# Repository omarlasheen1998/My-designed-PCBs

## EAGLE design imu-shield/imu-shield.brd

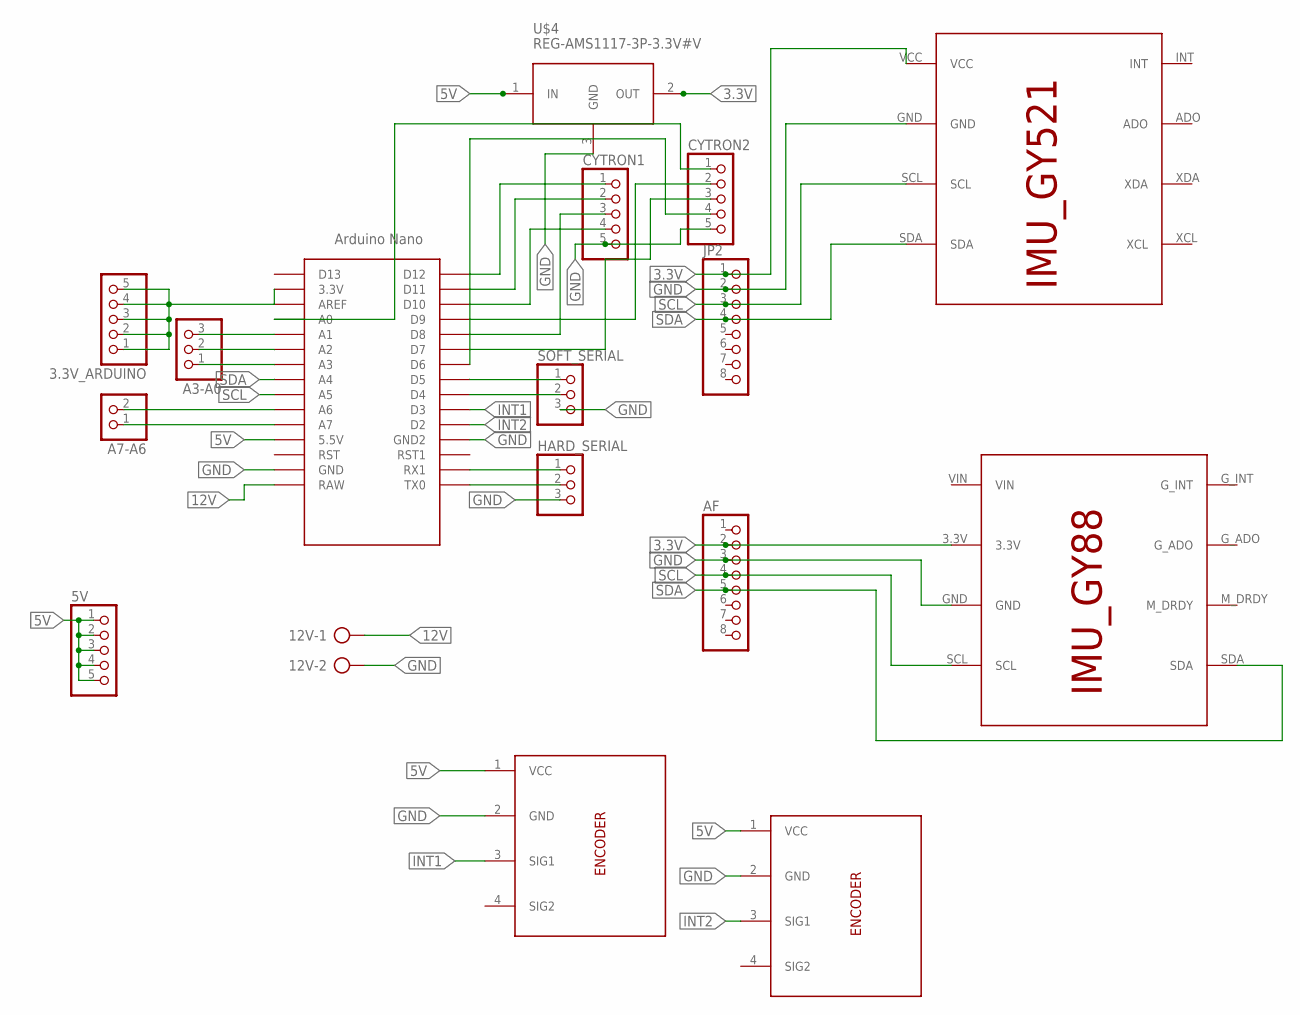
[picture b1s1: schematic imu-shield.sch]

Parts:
3.3V_ARDUINO, 5V: PINHD-1X5; 1X05
12V: AK300/2
A3-A0: PINHD-1X3; 1X03
A7-A6: PINHD-1X2; 1X02
AF: PINHD-1X8; 1X08
CYTRON1, CYTRON2: PINHD-1X5; 1X05
ENCODER1, ENCODER2: ENCODER; 1X04
HARD_SERIAL: PINHD-1X3; 1X03
JP2: PINHD-1X8; 1X08
SOFT_SERIAL: PINHD-1X3; 1X03
U$1: NANO
U$2: IMU_ROBOCON; IMU_GY521
U$3: IMU_MINESWEEPER; IMU_GY88
U$4: REG-AMS1117-3P-3.3V#V; REG-AMS1117-3P#V

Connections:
3.3V: AF.2, JP2.1, U$2.VCC, U$3.3.3V, U$4.2 (OUT)
5V: 5V.1, 5V.2, 5V.3, 5V.4, 5V.5, ENCODER1.1 (VCC), ENCODER2.1 (VCC), U$1.5V (5.5V), U$4.1 (IN)
12V: 12V.1, U$1.RAW
GND: 12V.2, AF.3, CYTRON1.5, CYTRON2.5, ENCODER1.2 (GND), ENCODER2.2 (GND), HARD_SERIAL.3, JP2.2, SOFT_SERIAL.3, U$1.GND, U$1.GND1 (GND2), U$2.GND, U$3.GND, U$4.3 (GND)
INT1: ENCODER2.3 (SIG1), U$1.D3
INT2: ENCODER1.3 (SIG1), U$1.D2
unnamed: SOFT_SERIAL.1, U$1.D5
unnamed: SOFT_SERIAL.2, U$1.D4
unnamed: HARD_SERIAL.1, U$1.RX1
unnamed: HARD_SERIAL.2, U$1.TX0
unnamed: CYTRON1.1, U$1.D12
unnamed: CYTRON1.2, U$1.D11
unnamed: CYTRON1.4, U$1.D10
unnamed: CYTRON2.2, U$1.D9
unnamed: CYTRON1.3, U$1.D8
unnamed: CYTRON2.3, U$1.D7
unnamed: CYTRON2.4, U$1.D6
unnamed: CYTRON2.1, U$1.A0
unnamed: A3-A0.1, U$1.A3
unnamed: A3-A0.2, U$1.A2
unnamed: A3-A0.3, U$1.A1
unnamed: A7-A6.1, U$1.A7
unnamed: A7-A6.2, U$1.A6
unnamed: 3.3V_ARDUINO.1, 3.3V_ARDUINO.2, 3.3V_ARDUINO.3, 3.3V_ARDUINO.4, 3.3V_ARDUINO.5, U$1.3.3V
SCL: AF.4, JP2.3, U$1.A5, U$2.SCL, U$3.SCL
SDA: AF.5, JP2.4, U$1.A4, U$2.SDA, U$3.SDA

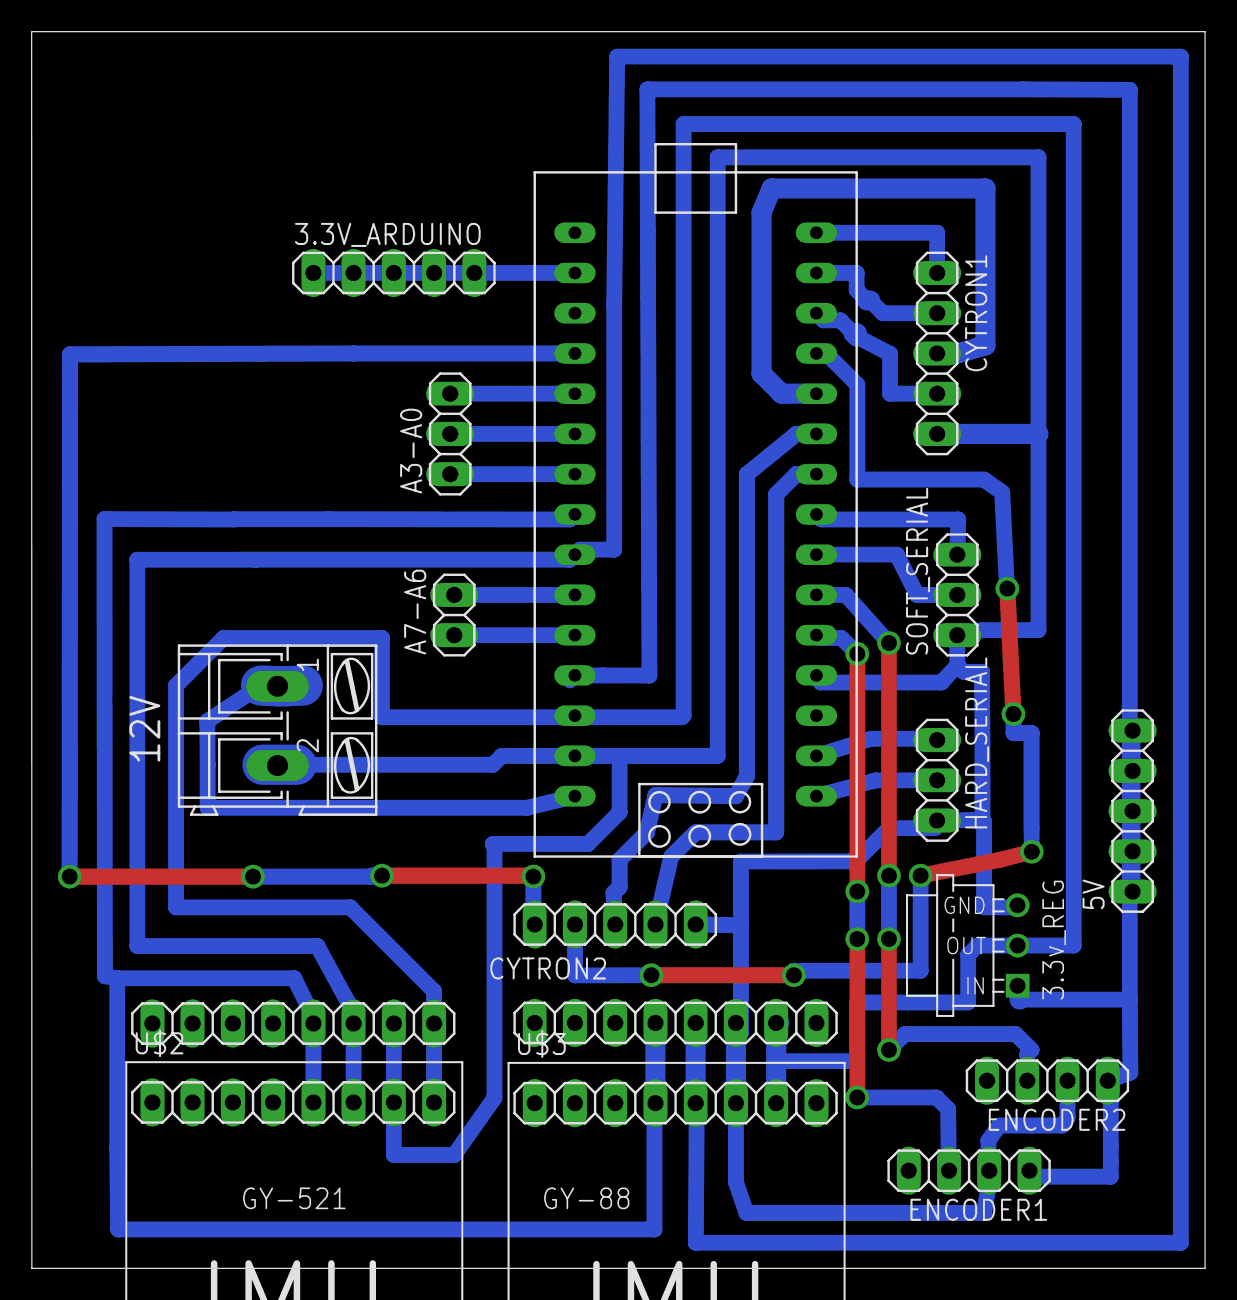
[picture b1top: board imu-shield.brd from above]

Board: 2 copper layers, 74.1 x 78.1 mm, 17 parts (0 on the bottom side), 26 nets.

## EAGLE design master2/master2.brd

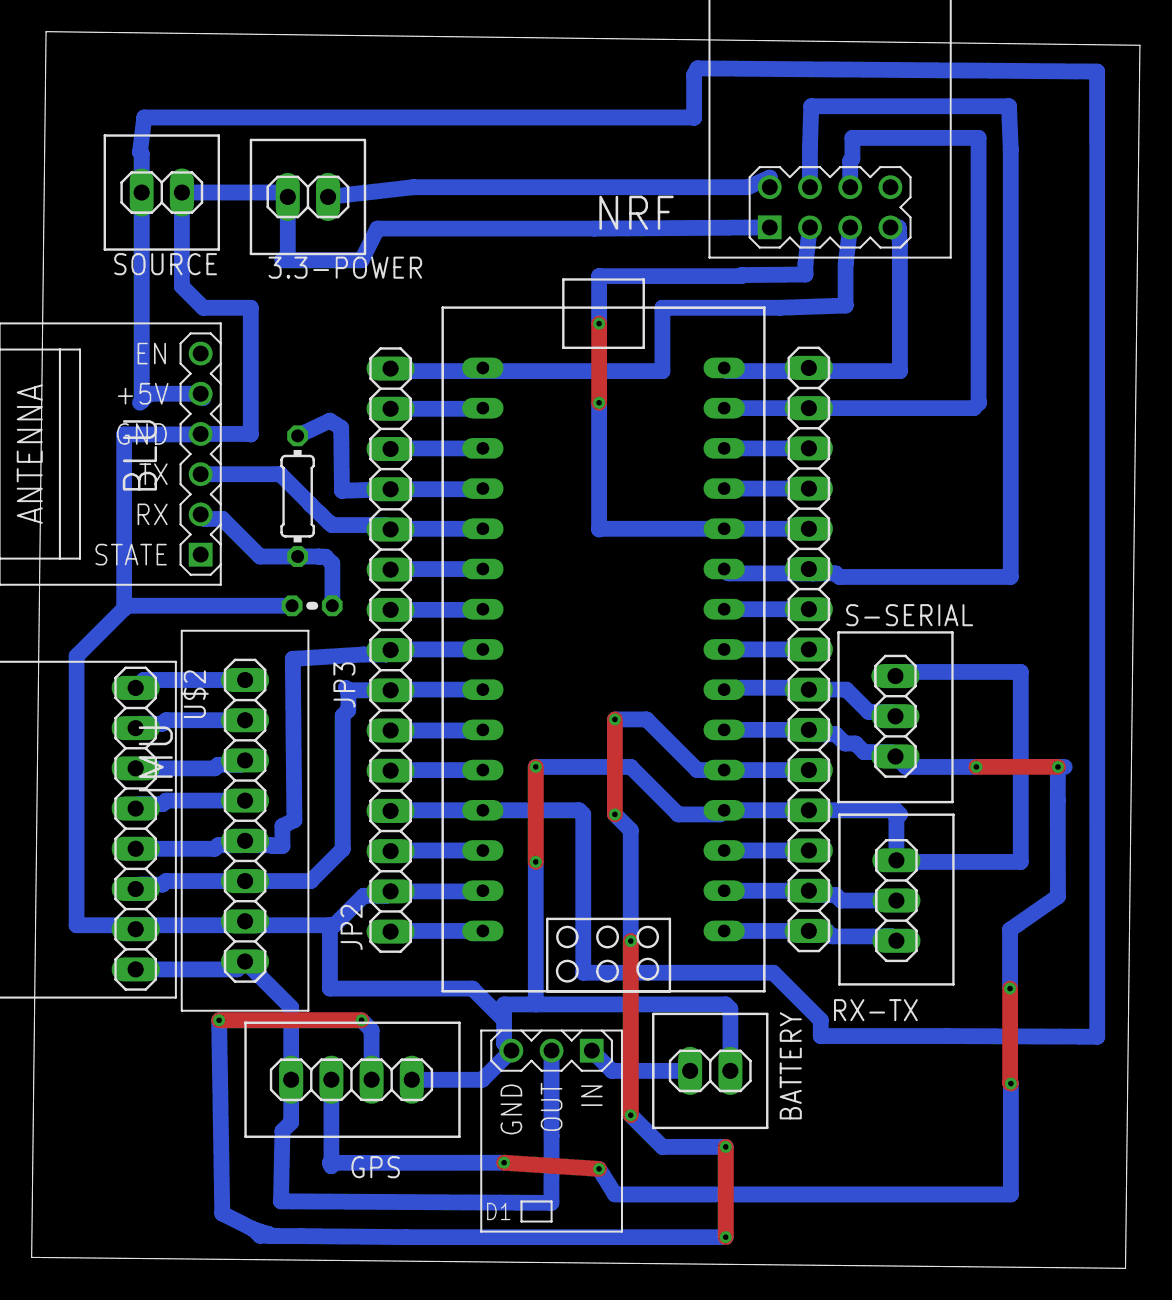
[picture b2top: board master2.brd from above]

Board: 2 copper layers, 70.0 x 78.1 mm, 16 parts (0 on the bottom side), 37 nets.

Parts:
3.3-POWER: 1X02_DATA
BATTERY: 1X02_DATA
GPS: 1X04_DATA
JP1, JP2: 1X15
JP3: 1X08_DATA
M1: WIRELESS-NRF24L01-PA-EXT
R1: 1k; 0204/7
R2: 2.2k; 0204V
RX-TX: 1X03_DATA
S-SERIAL: 1X03_DATA
SOURCE: 1X02_DATA
U$1: ARDUINO_NANO; NANO
U$2: IMU_ROBOCON; IMU_GY521
U$3: BLUETOOTH-HC-05; WIRELESS-BLUETOOTH-HC-05
U$4: REG-AMS1117-3P-3.3V; REG-AMS1117-3P

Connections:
3.3: GPS.4, JP3.8, U$2.VCC, U$4.2
3.3-POWER: 3.3-POWER.2, M1.2
A0: JP2.12, R1.2, U$1.A0
A1: JP2.11, U$1.A1, U$3.3
D2: GPS.2, JP1.11, U$1.D2
D3: GPS.3, JP1.10, S-SERIAL.3, U$1.D3
D4: JP1.9, S-SERIAL.2, U$1.D4
D5: JP1.8, U$1.D5
D6: JP1.7, U$1.D6
D7: JP1.6, M1.4, U$1.D7
D8: JP1.5, M1.3, U$1.D8
GND: 3.3-POWER.1, BATTERY.2, GPS.1, JP1.12, JP2.2, JP3.7, M1.1, R2.1, RX-TX.3, S-SERIAL.1, SOURCE.2, U$1.GND, U$1.GND1, U$2.GND, U$3.4, U$4.3
MISO: JP1.1, M1.7, U$1.D12
MOSI: JP1.2, M1.6, U$1.D11
unnamed: JP2.1, U$1.RAW
unnamed: R1.1, R2.2, U$3.2
unnamed: JP2.3, U$1.RST
unnamed: JP1.3, U$1.D10
unnamed: JP2.5, U$1.A7
unnamed: JP2.6, U$1.A6
unnamed: JP1.14, RX-TX.2, U$1.RX1
unnamed: JP3.1, U$2.INT
unnamed: JP2.9, U$1.A3
unnamed: JP2.10, U$1.A2
unnamed: JP3.2, U$2.ADO
unnamed: JP3.3, U$2.XCL
unnamed: JP2.13, U$1.AREF
unnamed: JP2.14, U$1.3.3V
unnamed: JP3.4, U$2.XDA
unnamed: JP1.4, U$1.D9
unnamed: JP1.13, U$1.RST1
unnamed: JP1.15, RX-TX.1, U$1.TX0
unnamed: BATTERY.1, U$4.1
S-CLC: JP2.15, M1.5, U$1.D13
SCL: JP2.7, JP3.6, U$1.A5, U$2.SCL
SDA: JP2.8, JP3.5, U$1.A4, U$2.SDA
VCC: JP2.4, SOURCE.1, U$1.5V, U$3.5

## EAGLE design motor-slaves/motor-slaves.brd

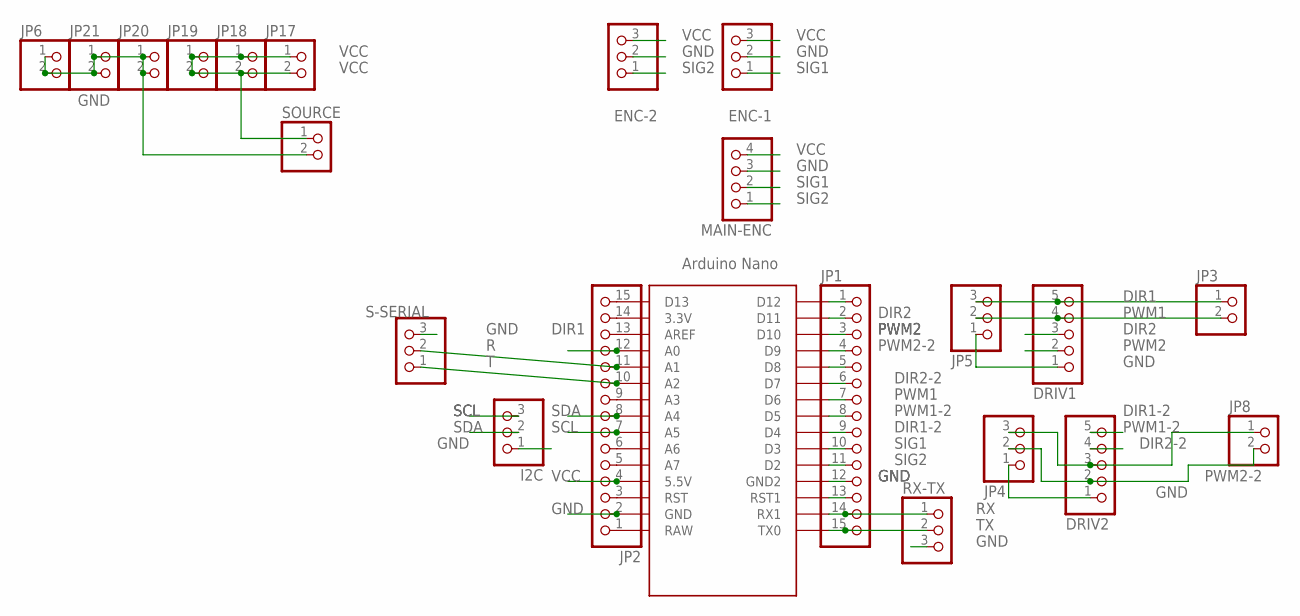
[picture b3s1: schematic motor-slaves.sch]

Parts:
DRIV1, DRIV2: PINHD-5_DATA; 1X05_DATA
ENC-1, ENC-2: PINHD-3_DATA; 1X03_DATA
I2C: PINHD-3_DATA; 1X03_DATA
JP1, JP2: PINHD-1X15; 1X15
JP3, JP8: PINHD-2_DATA; 1X02_DATA
JP4, JP5: PINHD-3_DATA; 1X03_DATA
JP6, JP17, JP18, JP19, JP20, JP21: PINHD-1X2; 1X02
MAIN-ENC: PINHD-4_DATA; 1X04_DATA
RX-TX: PINHD-3_DATA; 1X03_DATA
S-SERIAL: PINHD-3_DATA; 1X03_DATA
SOURCE: PINHD-1X2; 1X02
U$1: ARDUINO_NANO; NANO

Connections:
DIR1: DRIV1.5, JP2.12, JP3.1, JP5.3, U$1.A0
DIR1-2: DRIV2.5, JP1.9, U$1.D4
DIR2: DRIV1.3, JP1.2, U$1.D11
DIR2-2: DRIV2.3, JP1.6, JP4.3, JP8.1, U$1.D7
GND: DRIV1.1, DRIV2.1, ENC-1.2, ENC-2.2, I2C.1, JP1.12, JP2.2, JP4.1, JP5.1, JP6.1, JP6.2, JP20.1, JP20.2, JP21.1, JP21.2, MAIN-ENC.3, RX-TX.3, S-SERIAL.3, SOURCE.2, U$1.GND, U$1.GND1 (GND2)
unnamed: JP1.1, U$1.D12
unnamed: JP1.5, U$1.D8
unnamed: JP1.13, U$1.RST1
unnamed: JP2.1, U$1.RAW
unnamed: JP2.3, U$1.RST
unnamed: JP2.5, U$1.A7
unnamed: JP2.6, U$1.A6
unnamed: JP2.9, U$1.A3
unnamed: JP2.13, U$1.AREF
unnamed: JP2.14, U$1.3.3V
unnamed: JP2.15, U$1.D13
PWM1: DRIV1.4, JP1.7, JP3.2, JP5.2, U$1.D6
PWM1-2: DRIV2.4, JP1.8, U$1.D5
PWM2: DRIV1.2, JP1.3, U$1.D10
PWM2-2: DRIV2.2, JP1.4, JP4.2, JP8.2, U$1.D9
R: JP2.11, S-SERIAL.2, U$1.A1
RX: JP1.14, RX-TX.1, U$1.RX1
SCL: I2C.3, JP2.7, U$1.A5
SDA: I2C.2, JP2.8, U$1.A4
SIG1: ENC-1.1, JP1.10, MAIN-ENC.2, U$1.D3
SIG2: ENC-2.1, JP1.11, MAIN-ENC.1, U$1.D2
T: JP2.10, S-SERIAL.1, U$1.A2
TX: JP1.15, RX-TX.2, U$1.TX0
VCC: ENC-1.3, ENC-2.3, JP2.4, JP17.1, JP17.2, JP18.1, JP18.2, JP19.1, JP19.2, MAIN-ENC.4, SOURCE.1, U$1.5V (5.5V)

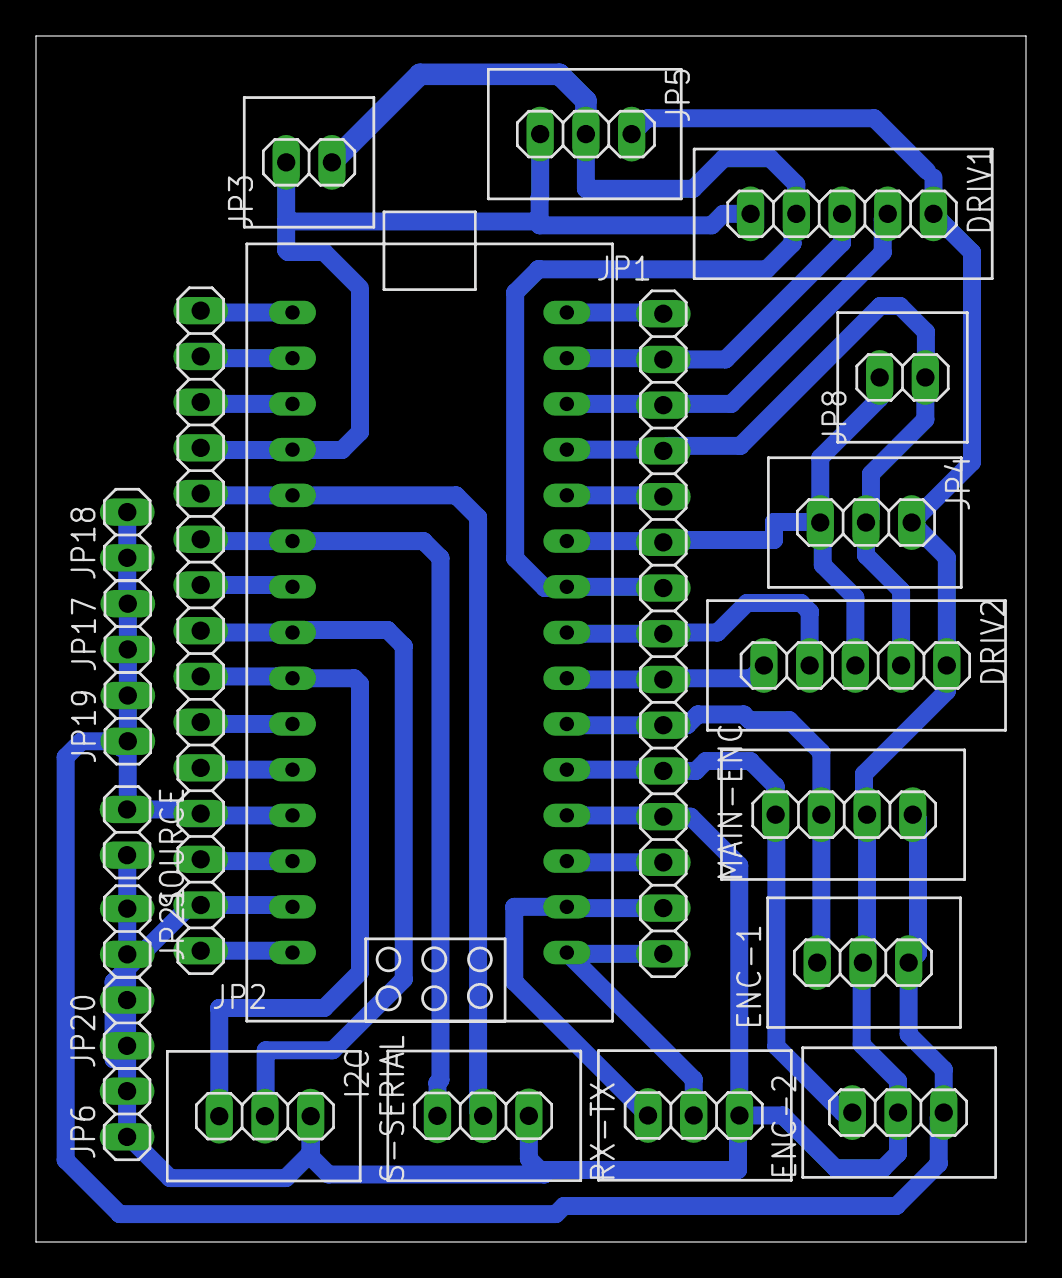
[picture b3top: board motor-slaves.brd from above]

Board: 2 copper layers, 55.0 x 67.0 mm, 22 parts (0 on the bottom side), 29 nets.

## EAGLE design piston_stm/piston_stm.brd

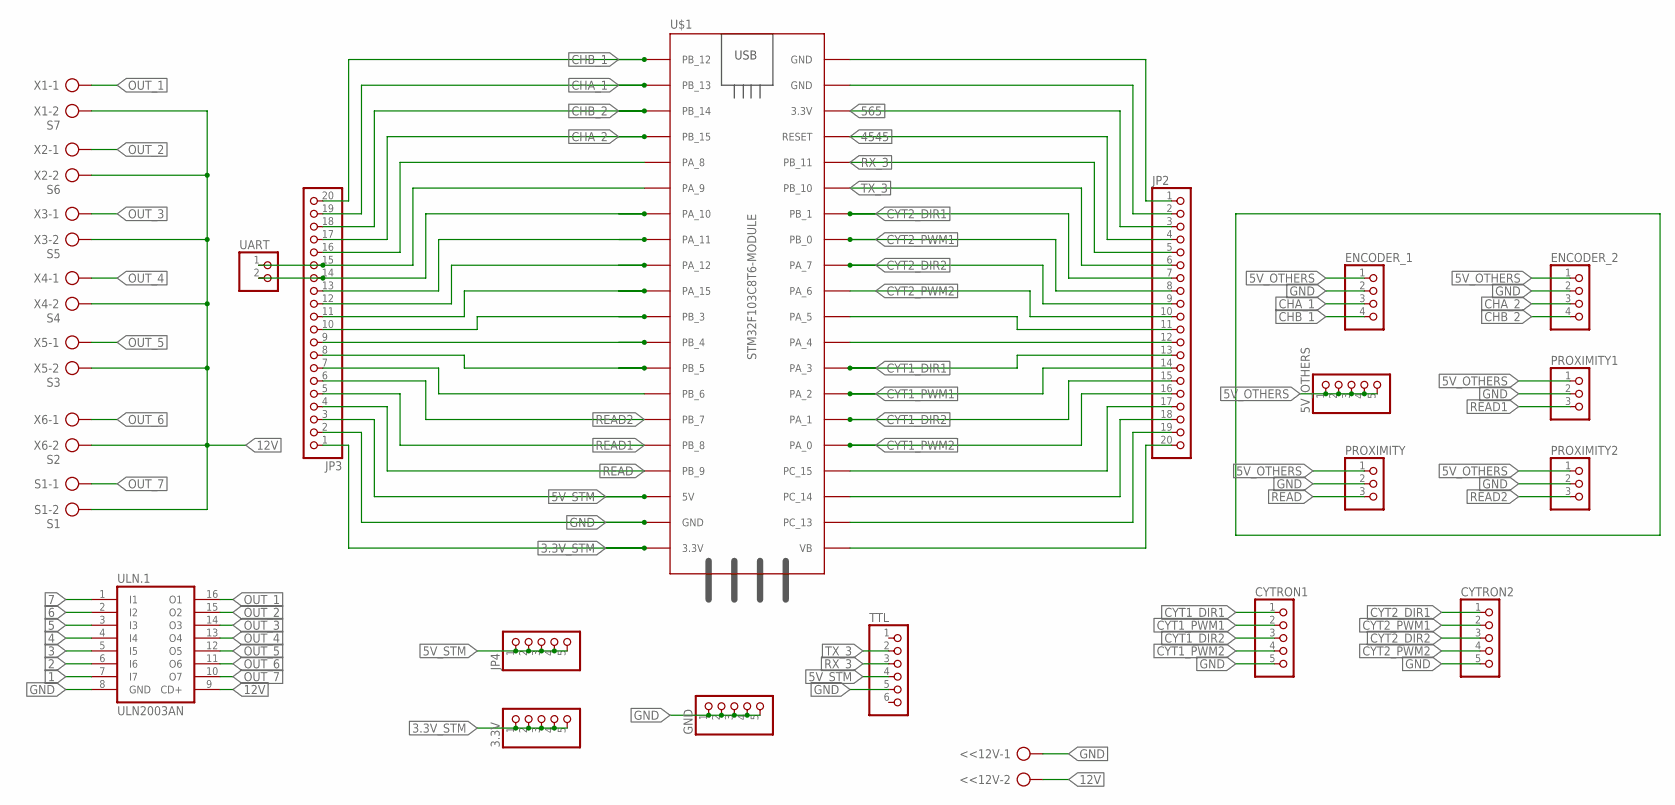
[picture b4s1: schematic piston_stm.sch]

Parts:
3.3V, 5V_OTHERS: PINHD-1X5; 1X05
<<12V: AK300/2
CYTRON1, CYTRON2: PINHD-5_DATA; DATA_5
ENCODER_1, ENCODER_2: PINHD-4_DATA; DATA_4
GND: PINHD-1X5; 1X05
JP2, JP3: PINHD-1X20; 1X20
JP4: PINHD-1X5; 1X05
PROXIMITY, PROXIMITY1, PROXIMITY2: PINHD-3_DATA; DATA_3
S1: S1; AK300/2
TTL: PINHD-6_DATA; DATA_6
U$1: STM32F103C8T6-MODULE
UART: PINHD-2_DATA; DATA_2
ULN.1: ULN2003AN; DIL16
X1: S7; AK300/2
X2: S6; AK300/2
X3: S5; AK300/2
X4: S4; AK300/2
X5: S3; AK300/2
X6: S2; AK300/2

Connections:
0: JP3.7, U$1.PB_6
1: JP3.13, U$1.PA_11, ULN.1.7 (I7)
2: JP3.12, U$1.PA_12, ULN.1.6 (I6)
3: JP3.11, U$1.PA_15, ULN.1.5 (I5)
3.3V_STM: 3.3V.1, 3.3V.2, 3.3V.3, 3.3V.4, 3.3V.5, JP3.1, U$1.3.3V_1 (3.3V)
4: JP3.10, U$1.PB_3, ULN.1.4 (I4)
5: JP3.9, U$1.PB_4, ULN.1.3 (I3)
5V_OTHERS: 5V_OTHERS.1, 5V_OTHERS.2, 5V_OTHERS.3, 5V_OTHERS.4, 5V_OTHERS.5, ENCODER_1.1, ENCODER_2.1, PROXIMITY.1, PROXIMITY1.1, PROXIMITY2.1
5V_STM: JP3.3, JP4.1, JP4.2, JP4.3, JP4.4, JP4.5, TTL.4, U$1.5V
6: JP3.8, U$1.PB_5, ULN.1.2 (I2)
7: JP2.12, U$1.PA_4, ULN.1.1 (I1)
12V: <<12V.2, S1.2, ULN.1.9 (CD+), X1.2, X2.2, X3.2, X4.2, X5.2, X6.2
565: JP2.3, U$1.3.3V_2 (3.3V)
4545: JP2.4, U$1.RESET
54454: JP3.14, U$1.PA_10, UART.2
CHA_1: ENCODER_1.3, JP3.19, U$1.PB_13
CHA_2: ENCODER_2.3, JP3.17, U$1.PB_15
CHB_1: ENCODER_1.4, JP3.20, U$1.PB_12
CHB_2: ENCODER_2.4, JP3.18, U$1.PB_14
CYT1_DIR1: CYTRON1.1, JP2.13, U$1.PA_3
CYT1_DIR2: CYTRON1.3, JP2.15, U$1.PA_1
CYT1_PWM1: CYTRON1.2, JP2.14, U$1.PA_2
CYT1_PWM2: CYTRON1.4, JP2.16, U$1.PA_0
CYT2_DIR1: CYTRON2.1, JP2.7, U$1.PB_1
CYT2_DIR2: CYTRON2.3, JP2.9, U$1.PA_7
CYT2_PWM1: CYTRON2.2, JP2.8, U$1.PB_0
CYT2_PWM2: CYTRON2.4, JP2.10, U$1.PA_6
GND: <<12V.1, CYTRON1.5, CYTRON2.5, ENCODER_1.2, ENCODER_2.2, GND.1, GND.2, GND.3, GND.4, GND.5, JP2.1, JP2.2, JP3.2, PROXIMITY.2, PROXIMITY1.2, PROXIMITY2.2, TTL.5, U$1.GND_1 (GND), U$1.GND_2 (GND), U$1.GND_3 (GND), ULN.1.8 (GND)
unnamed: JP2.11, U$1.PA_5
unnamed: JP2.20, U$1.VB
unnamed: JP2.19, U$1.PC_13
unnamed: JP2.18, U$1.PC_14
unnamed: JP2.17, U$1.PC_15
unnamed: JP3.16, U$1.PA_8
unnamed: JP3.15, U$1.PA_9, UART.1
OUT_1: ULN.1.16 (O1), X1.1
OUT_2: ULN.1.15 (O2), X2.1
OUT_3: ULN.1.14 (O3), X3.1
OUT_4: ULN.1.13 (O4), X4.1
OUT_5: ULN.1.12 (O5), X5.1
OUT_6: ULN.1.11 (O6), X6.1
OUT_7: S1.1, ULN.1.10 (O7)
READ: JP3.4, PROXIMITY.3, U$1.PB_9
READ1: JP3.5, PROXIMITY1.3, U$1.PB_8
READ2: JP3.6, PROXIMITY2.3, U$1.PB_7
RX_3: JP2.5, TTL.3, U$1.PB_11
TX_3: JP2.6, TTL.2, U$1.PB_10

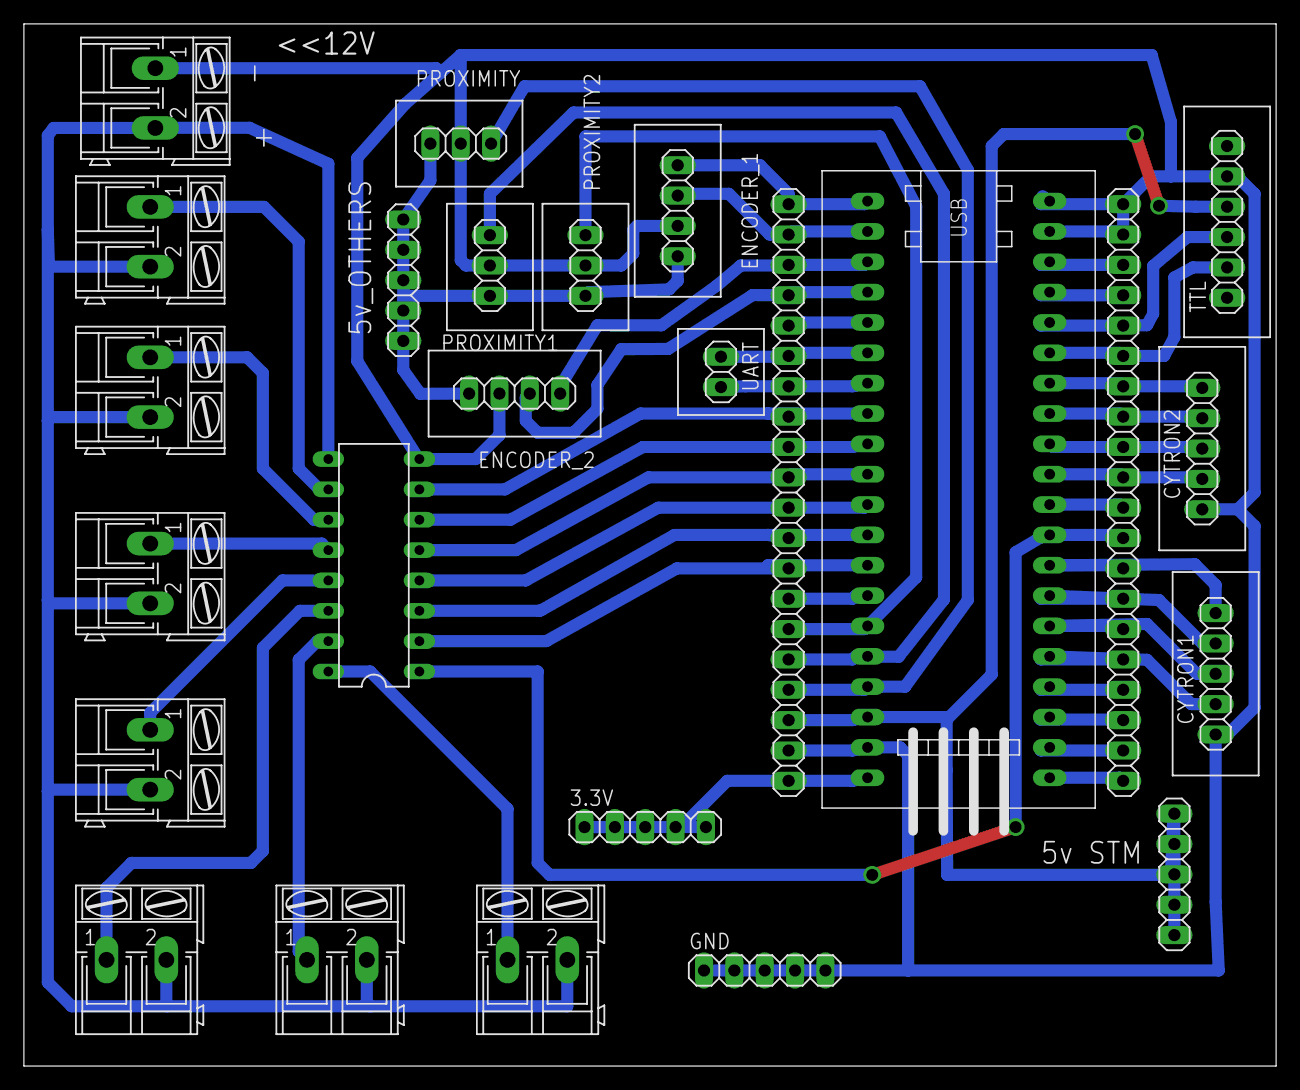
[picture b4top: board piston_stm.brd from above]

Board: 2 copper layers, 104.8 x 87.2 mm, 25 parts (0 on the bottom side), 47 nets.

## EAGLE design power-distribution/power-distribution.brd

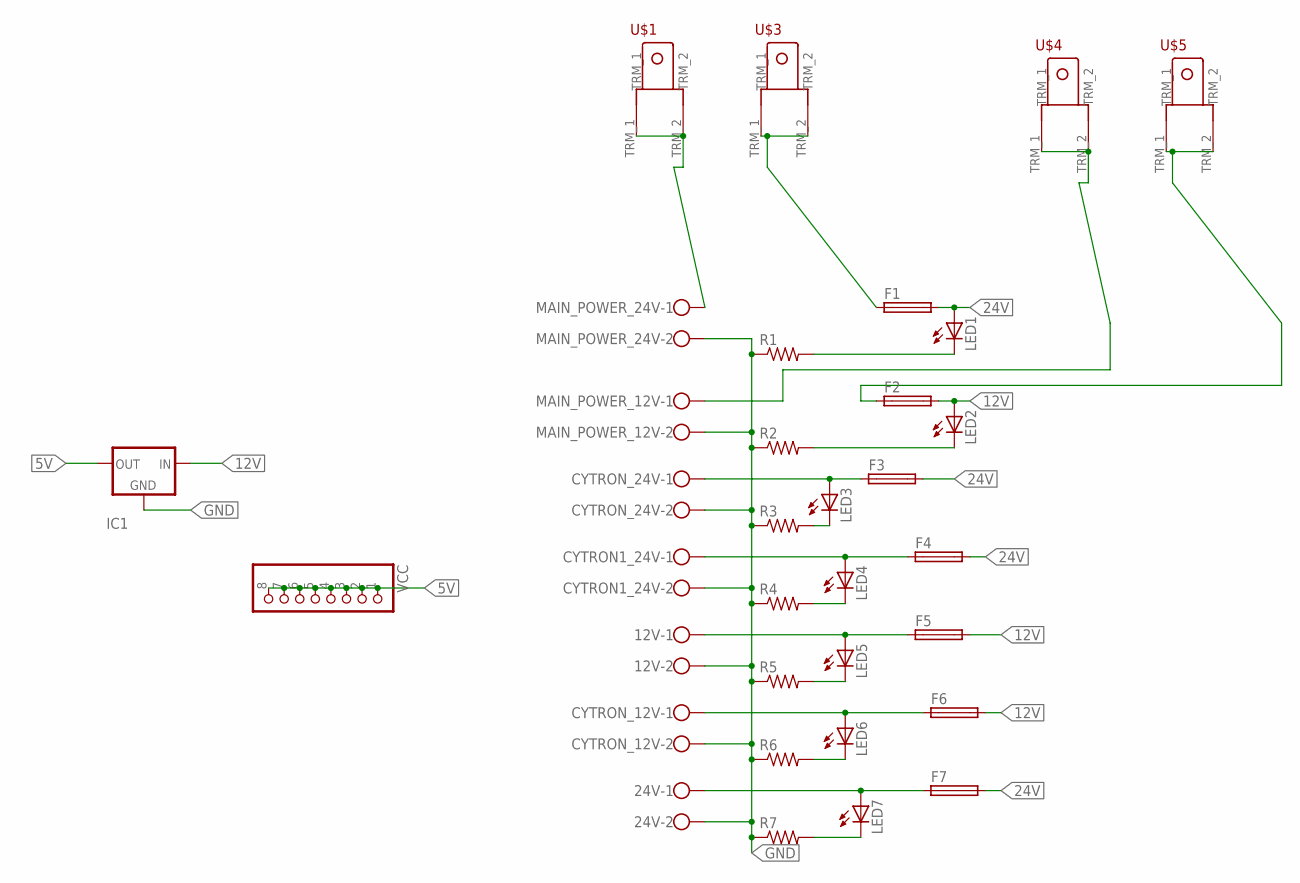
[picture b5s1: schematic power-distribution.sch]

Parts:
12V, 24V: W237-113
CYTRON1_24V: W237-113
CYTRON_12V, CYTRON_24V: W237-113
F1, F2, F3, F4, F5, F6, F7: SH22,5A
IC1: 79XX-TO3; TO3-79
LED1, LED2: LED5MM
LED3, LED4, LED5, LED6, LED7: LED3MM
MAIN_POWER_12V, MAIN_POWER_24V: W237-113
R1, R3, R4, R6, R7: R-US_0204/5; 0204/5
R2: R-US_0207/12; 0207/12
R5: R-US_0207/10; 0207/10
U$1, U$3, U$4, U$5: TERMINAL_EDITED
VCC: PINHD-1X8; 1X08

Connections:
5V: IC1.1 (OUT), VCC.1, VCC.2, VCC.3, VCC.4, VCC.5, VCC.6, VCC.7, VCC.8
12V: F2.2, F5.2, F6.2, IC1.3 (IN), LED2.A
24V: F1.2, F3.2, F4.2, F7.2, LED1.A
GND: 12V.2, 24V.2, CYTRON1_24V.2, CYTRON_12V.2, CYTRON_24V.2, IC1.2 (GND), MAIN_POWER_12V.2, MAIN_POWER_24V.2, R1.1, R2.1, R3.1, R4.1, R5.1, R6.1, R7.1
unnamed: CYTRON_12V.1, F6.1, LED6.A
unnamed: LED1.K (C), R1.2
unnamed: MAIN_POWER_24V.1, U$1.TRM_1, U$1.TRM_2
unnamed: LED2.K (C), R2.2
unnamed: MAIN_POWER_12V.1, U$4.TRM_1, U$4.TRM_2
unnamed: 24V.1, F7.1, LED7.A
unnamed: CYTRON_24V.1, F3.1, LED3.A
unnamed: LED3.K (C), R3.2
unnamed: CYTRON1_24V.1, F4.1, LED4.A
unnamed: LED4.K (C), R4.2
unnamed: 12V.1, F5.1, LED5.A
unnamed: LED5.K (C), R5.2
unnamed: F1.1, U$3.TRM_1, U$3.TRM_2
unnamed: F2.1, U$5.TRM_1, U$5.TRM_2
unnamed: LED6.K (C), R6.2
unnamed: LED7.K (C), R7.2

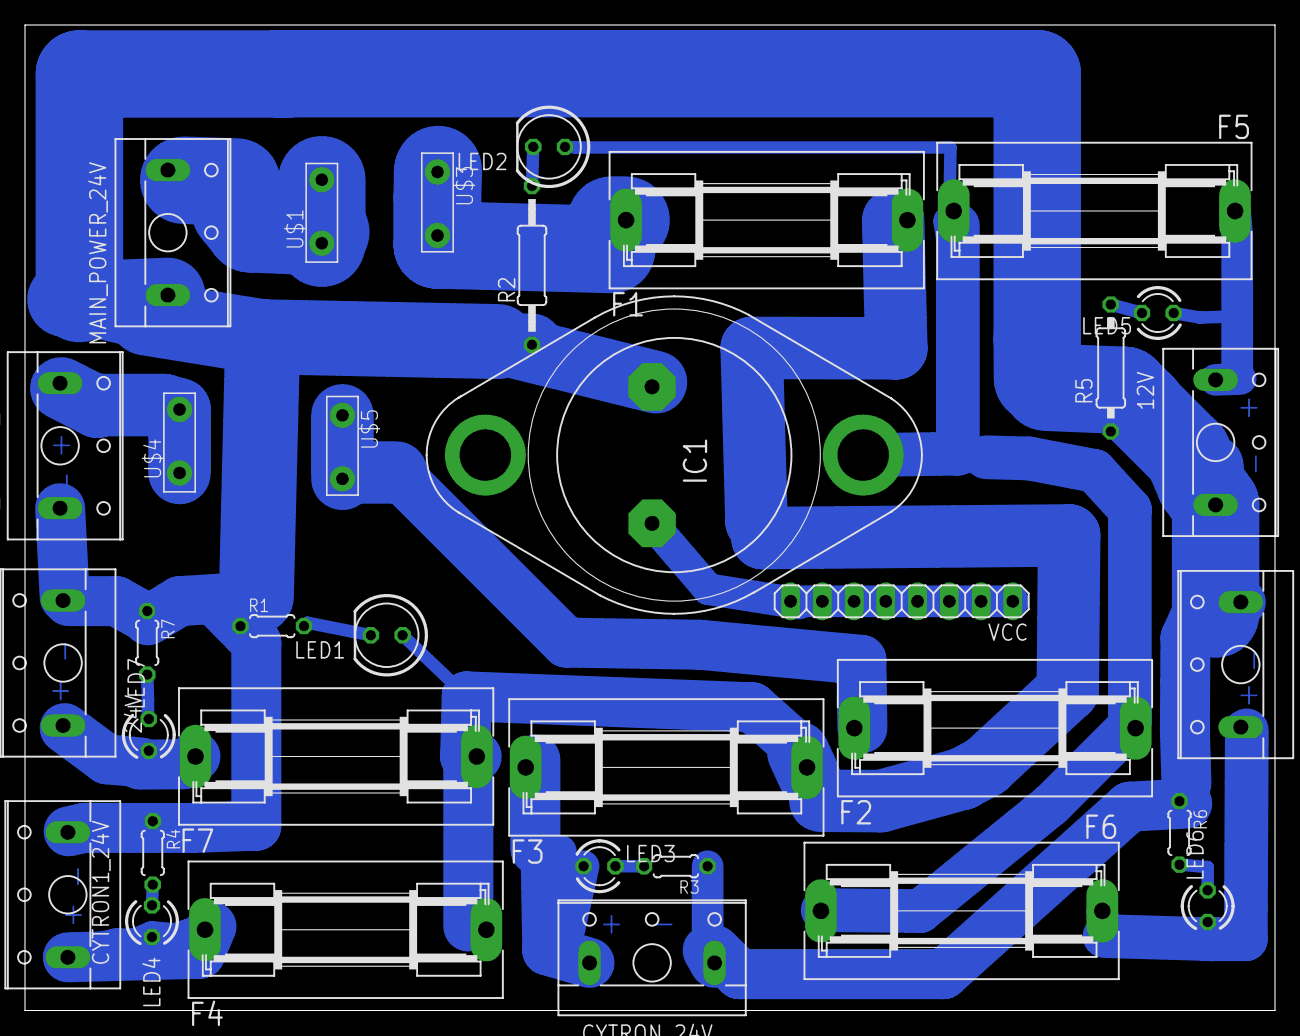
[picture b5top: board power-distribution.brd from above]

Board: 2 copper layers, 100.0 x 78.8 mm, 34 parts (0 on the bottom side), 20 nets.

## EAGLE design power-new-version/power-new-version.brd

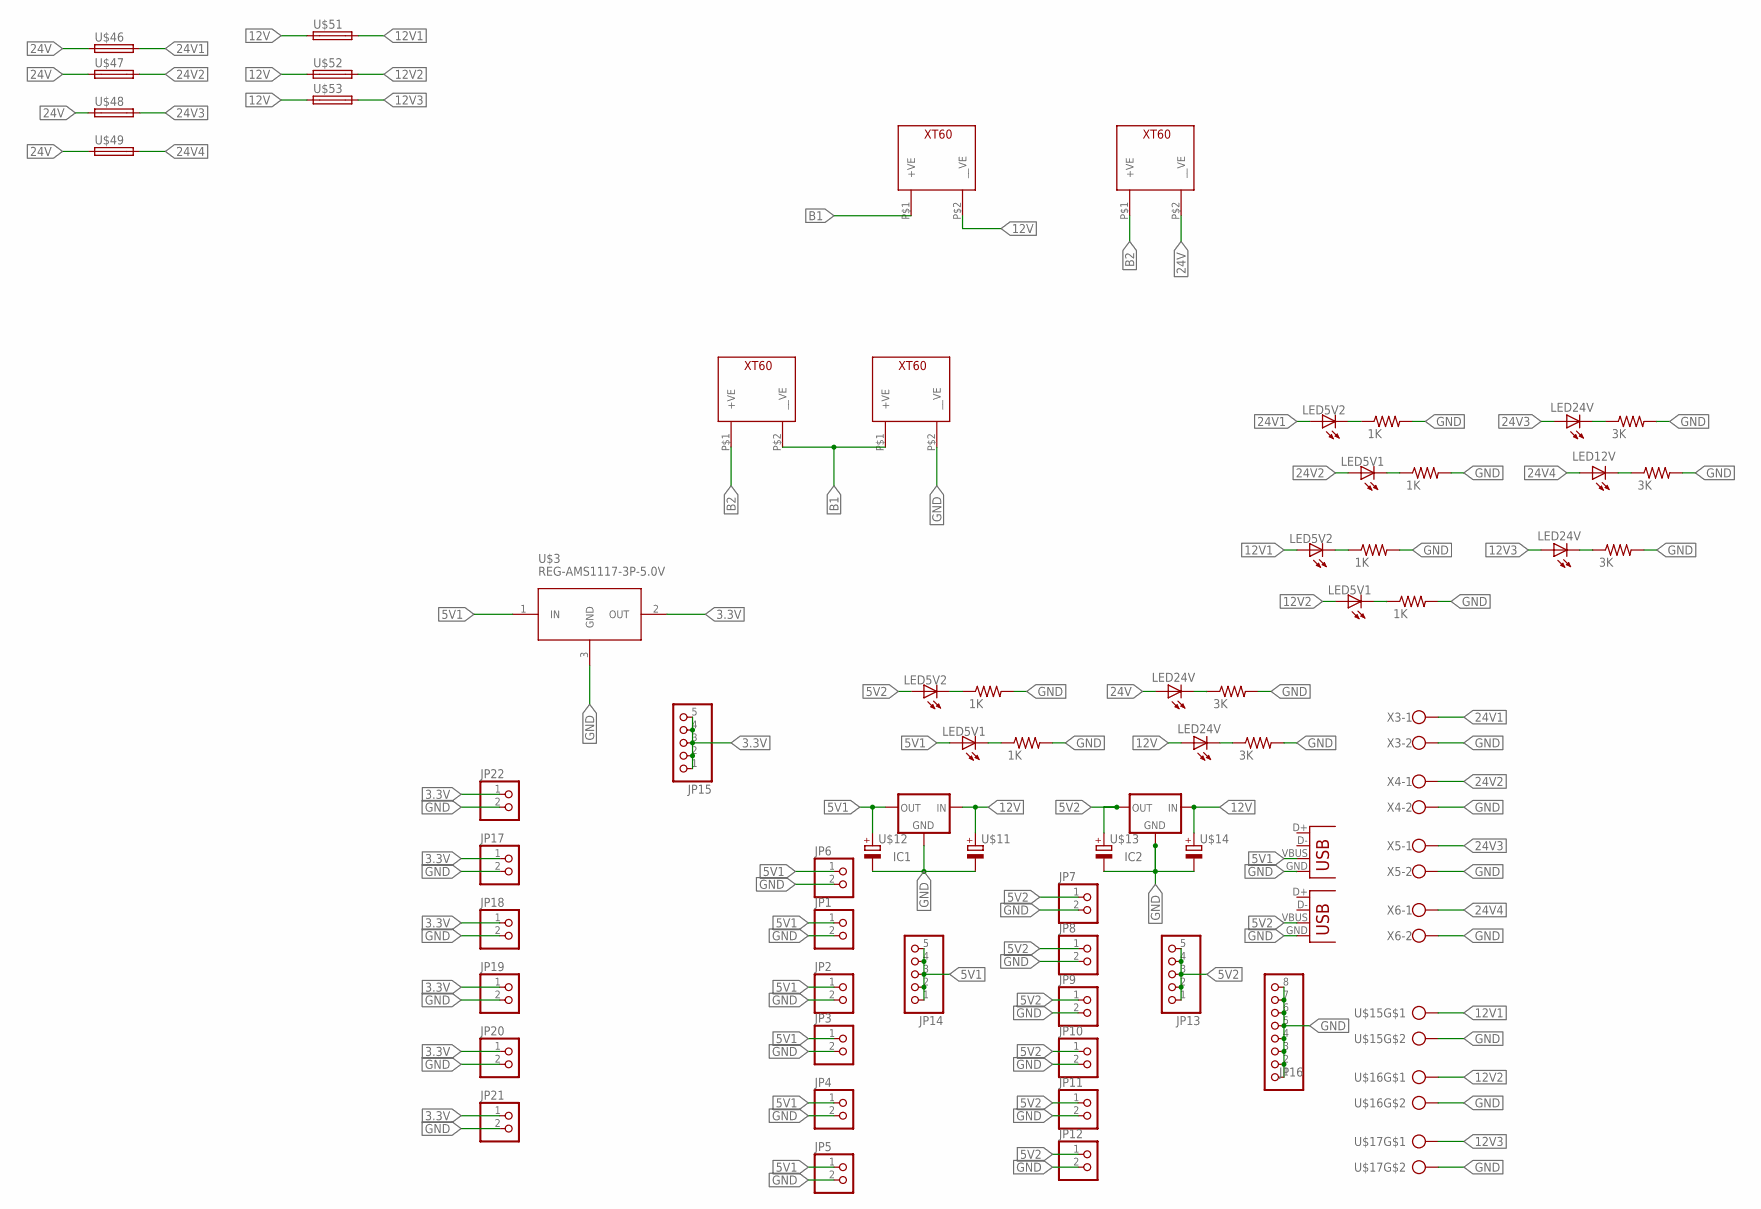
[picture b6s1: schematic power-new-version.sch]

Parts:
1K, 1K1, 1K2: 1K; 0204/7
IC1, IC2: 78XX-METAL; TO3-79
JP1, JP2, JP3, JP4, JP5, JP6, JP7, JP8, JP9, JP10, JP11, JP12, JP17, JP18, JP19, JP20, JP21, JP22: PINHD-2_DATA; 1X02_DATA
JP13, JP14, JP15: PINHD-1X5; 1X05
JP16: PINHD-1X8; 1X08
U$1, U$18, U$25: LED5V2; LED3MM
U$2, U$19, U$26: LED5V1; LED3MM
U$3: REG-AMS1117-3P-5.0V; REG-AMS1117-3P
U$4, U$20, U$27, U$28: LED24V; LED3MM
U$6, U$10, U$44, U$45: XT60_CONNECTOR; XT60
U$7, U$22, U$29: 1K; 0204/7
U$8, U$9, U$23, U$24, U$31: 3K; 0204/7
U$11, U$12, U$13, U$14: CAP_POL; E3,5-8
U$15, U$16, U$17: CON_PTR_2; AK300/2
U$21: LED12V; LED3MM
U$46, U$47, U$48, U$49, U$51, U$52, U$53: FUSE_PANNEL_MOUNTPANEL_MOUNT; PANEL_MOUNT
X1, X2: USB-A-H
X3, X4, X5, X6: ROSTA.POWER; W239-302

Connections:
3.3V: JP15.1, JP15.2, JP15.3, JP15.4, JP15.5, JP17.1, JP18.1, JP19.1, JP20.1, JP21.1, JP22.1, U$3.2 (OUT)
5V1: IC1.1 (OUT), JP1.1, JP2.1, JP3.1, JP4.1, JP5.1, JP6.1, JP14.1, JP14.2, JP14.3, JP14.4, JP14.5, U$2.A, U$3.1 (IN), U$12.+, X1.VBUS
5V2: IC2.1 (OUT), JP7.1, JP8.1, JP9.1, JP10.1, JP11.1, JP12.1, JP13.1, JP13.2, JP13.3, JP13.4, JP13.5, U$1.A, U$13.+, X2.VBUS
12V: IC1.3 (IN), IC2.3 (IN), U$11.+, U$14.+, U$28.A, U$45.P$2 (__VE), U$51.P$1 (1), U$52.P$1 (1), U$53.P$1 (1)
12V1: U$15.1, U$25.A, U$51.P$2 (2)
12V2: U$16.1, U$26.A, U$52.P$2 (2)
12V3: U$17.1, U$27.A, U$53.P$2 (2)
24V: U$4.A, U$44.P$2 (__VE), U$46.P$1 (1), U$47.P$1 (1), U$48.P$1 (1), U$49.P$1 (1)
24V1: U$18.A, U$46.P$2 (2), X3.1
24V2: U$19.A, U$47.P$2 (2), X4.1
24V3: U$20.A, U$48.P$2 (2), X5.1
24V4: U$21.A, U$49.P$2 (2), X6.1
B1: U$6.P$2 (__VE), U$10.P$1 (+VE), U$45.P$1 (+VE)
B2: U$6.P$1 (+VE), U$44.P$1 (+VE)
GND: 1K.2, 1K1.2, 1K2.2, IC1.2 (GND), IC2.2 (GND), JP1.2, JP2.2, JP3.2, JP4.2, JP5.2, JP6.2, JP7.2, JP8.2, JP9.2, JP10.2, JP11.2, JP12.2, JP16.1, JP16.2, JP16.3, JP16.4, JP16.5, JP16.6, JP16.7, JP16.8, JP17.2, JP18.2, JP19.2, JP20.2, JP21.2, JP22.2, U$3.3 (GND), U$7.2, U$8.2, U$9.2, U$10.P$2 (__VE), U$11.-, U$12.-, U$13.-, U$14.-, U$15.2, U$16.2, U$17.2, U$22.2, U$23.2, U$24.2, U$29.2, U$31.2, X1.GND, X2.GND, X3.2, X4.2, X5.2, X6.2
unnamed: 1K1.1, U$18.K (C)
unnamed: U$19.K (C), U$22.1
unnamed: U$21.K (C), U$23.1
unnamed: U$20.K (C), U$24.1
unnamed: 1K2.1, U$25.K (C)
unnamed: U$26.K (C), U$29.1
unnamed: 1K.1, U$1.K (C)
unnamed: U$2.K (C), U$7.1
unnamed: U$8.1, U$28.K (C)
unnamed: U$4.K (C), U$9.1
unnamed: U$27.K (C), U$31.1

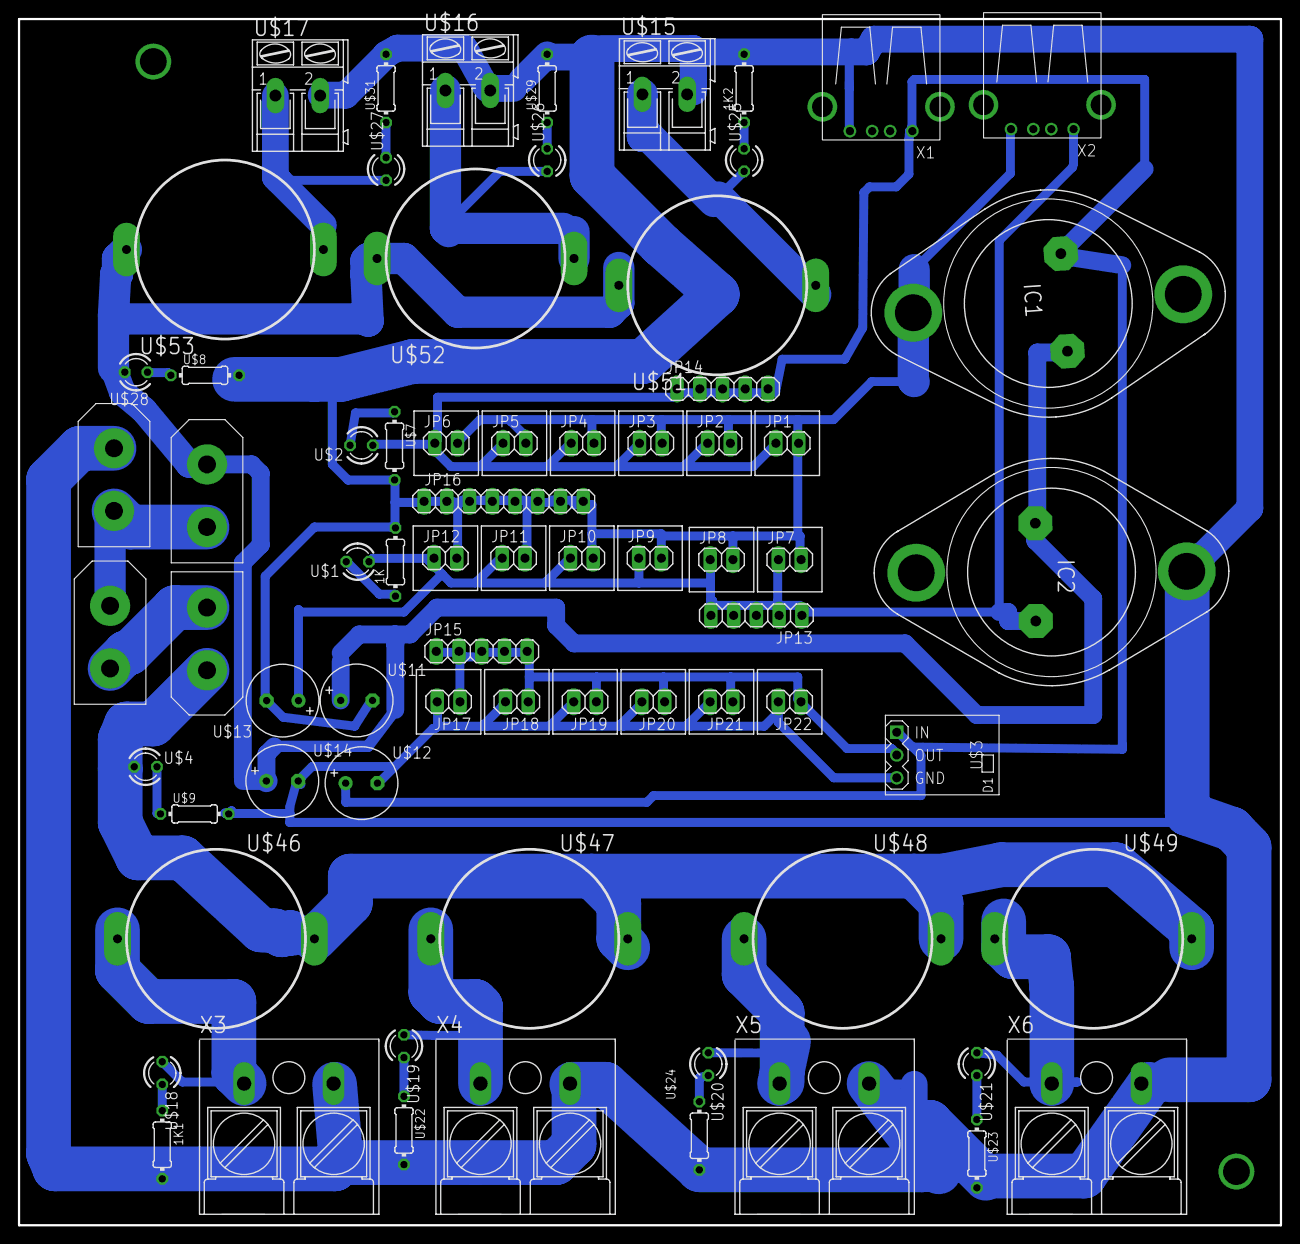
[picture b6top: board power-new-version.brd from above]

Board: 2 copper layers, 141.0 x 134.8 mm, 71 parts (0 on the bottom side), 26 nets.
